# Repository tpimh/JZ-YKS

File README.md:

JZ-YKS
======

My first hardware mini-module

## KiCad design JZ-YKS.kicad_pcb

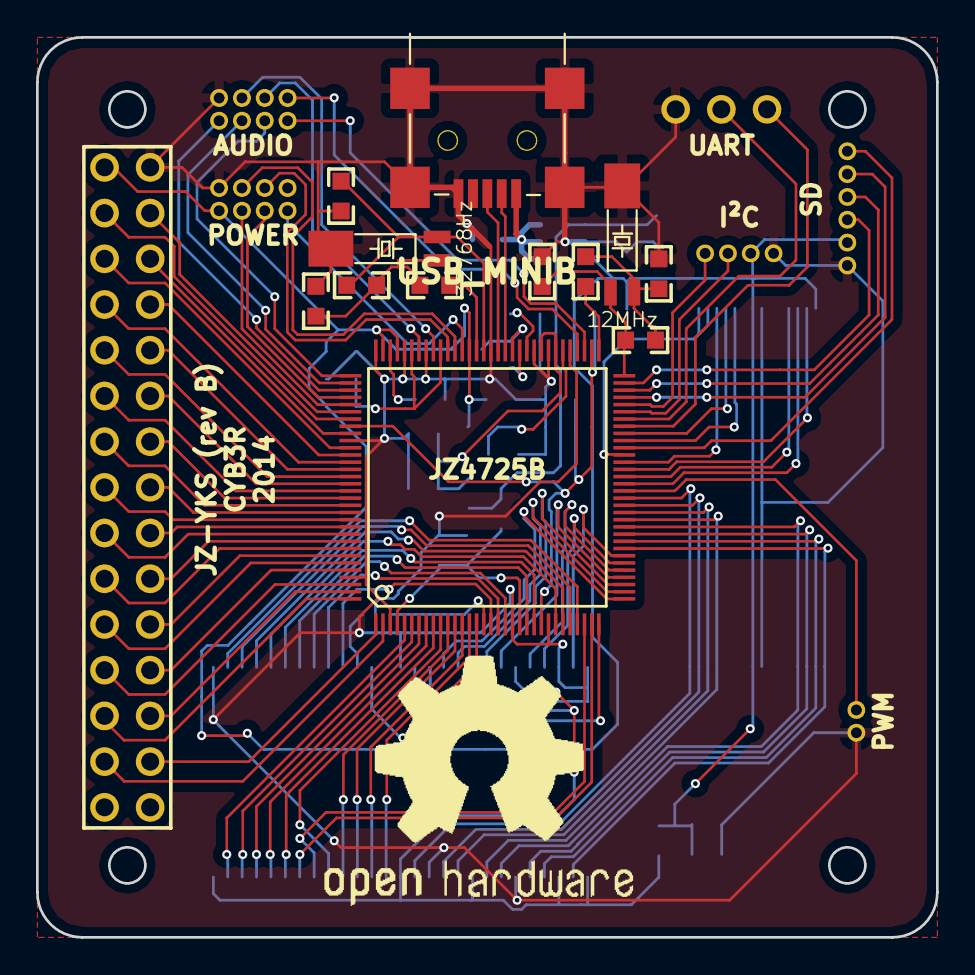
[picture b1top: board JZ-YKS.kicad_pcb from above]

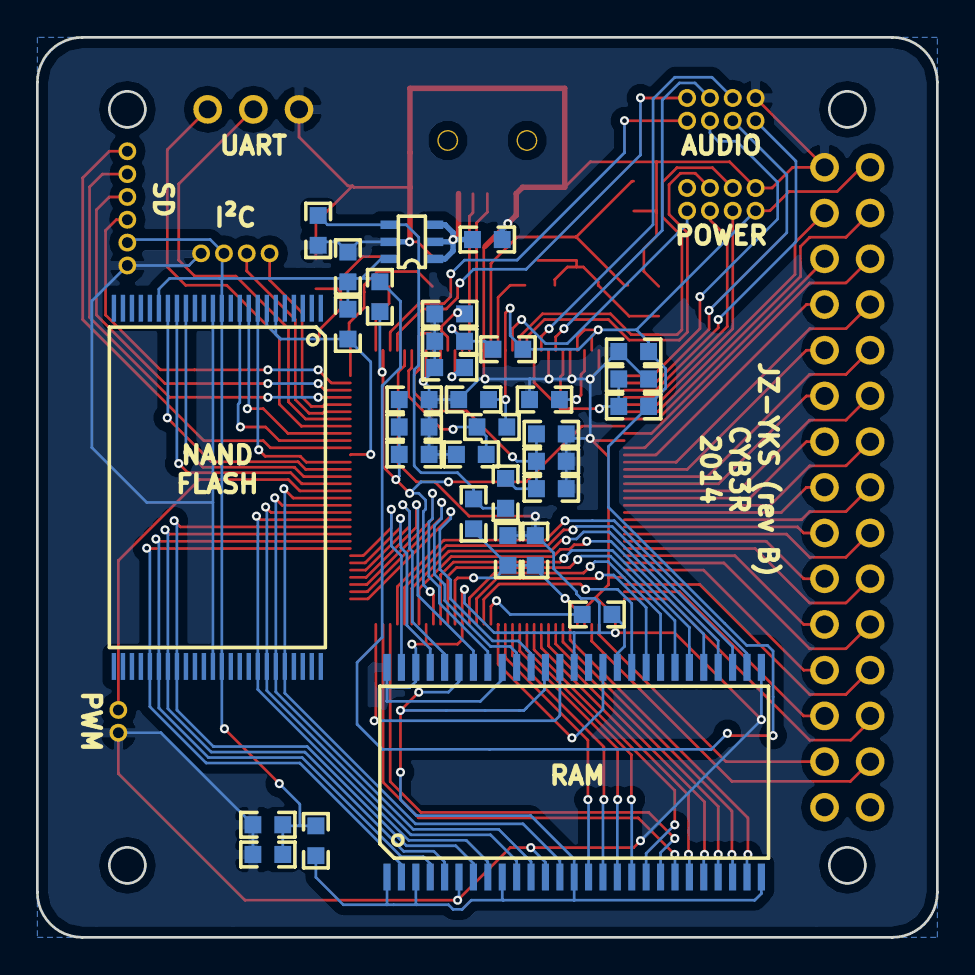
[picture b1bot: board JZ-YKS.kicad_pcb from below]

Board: 2 copper layers, 50.0 x 50.0 mm, 52 parts (33 on the bottom side), 116 nets.

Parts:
C1, C3, C4, C5, C9, C13, C27: 0.1uF; size-0603
C2, C6, C14, C15, C28: 10uF; size-0603
C7, C8, C10, C29, C30, C31: 1uF; size-0603
C11, C12: 0.01uF; size-0603
C16, C17, C18, C19: 22pF; size-0603
FB1, FB2, FB3, FB5, FB6, FB7, FB9: BKP1608HS121; size-0603
IC1: JZ4725; JZ-LQFP128
J1: USB_MINIB; CON_USB_MB
R1: 10k; size-0603
R2, R3, R6: 33; size-0603
R4: 10M; size-0603
R5: 1M; size-0603
R7: 100k; size-0603
U1: PINHEAD30; pinhead-double-2.54mm-30
U2, U9: PINHEAD8; pinhead-double-1.27mm-8
U3: VREG-DUAL; sot23-6
U4: HY27UG088G5M; tsop48
U5: P3V56S40ETP-G6; tsop54
U6: PINHEAD6; pinhead-1.27mm-6
U7: PINHEAD4; pinhead-1.27mm-4
U8: PINHEAD3; pinhead-2.54mm-3
U10: PINHEAD2; pinhead-1.27mm-2
X1: 32768Hz; crystal
X2: 12MHz; crystal

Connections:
+1.8V: C30.2, FB2.2, FB7.2, U3.4
+3.3V: C1.1, C11.1, C27.1, C28.1, C31.2, FB1.2, FB3.2, FB5.2, FB6.2, FB9.2, IC1.83, IC1.93, IC1.95, R7.1, U1.2, U2.2, U3.6, U4.12, U4.19, U4.37, U6.2, U7.2
/VDDCORE: C5.1, C6.1, FB2.1, IC1.4, IC1.21
/VDDIO: C2.1, C3.1, C4.1, FB1.1, IC1.24, IC1.66, IC1.104
/memory/MEM_VCC: FB9.1, U5.1, U5.3, U5.9, U5.14, U5.27, U5.43, U5.49
A0: IC1.8, U5.23
A1: IC1.7, U5.24
A2: IC1.6, U5.25
A3: IC1.5, U5.26
A4: IC1.29, U5.29
A5: IC1.28, U5.30
A6: IC1.27, U5.31
A7: IC1.26, U5.32
A8: IC1.23, U5.33
A9: IC1.22, U5.34
A10: IC1.9, U5.22
A11: IC1.19, U5.35
A12: IC1.18, U5.36
A13: IC1.30, U5.20
A14: IC1.31, U5.21
A15: IC1.50, U4.16
A16: IC1.49, U4.17
ADIN0: IC1.67, U9.8
ADIN1: IC1.68, U9.7
B1: IC1.105, U1.5
B2: IC1.1, U1.27
B3: IC1.128, U1.26
B4: IC1.127, U1.25
B5: IC1.126, U1.24
B6: IC1.124, U1.23
B7: IC1.123, U1.22
BOOT_0: IC1.101, U2.4
BOOT_1: IC1.100, U2.6
CAS: IC1.12, U5.17
CKE: IC1.17, U5.37
CKO: IC1.16, R6.2
CS1: IC1.56, U4.9
CS2: IC1.55, U4.10
D0: IC1.40, U4.29, U5.2
D1: IC1.41, U4.30, U5.4
D2: IC1.42, U4.31, U5.5
D3: IC1.43, U4.32, U5.7
D4: IC1.44, U4.41, U5.8
D5: IC1.45, U4.42, U5.10
D6: IC1.46, U4.43, U5.11
D7: IC1.47, U4.44, U5.13
D8: IC1.32, U5.42
D9: IC1.33, U5.44
D10: IC1.34, U5.45
D11: IC1.35, U5.47
D12: IC1.36, U5.48
D13: IC1.37, U5.50
D14: IC1.38, U5.51
D15: IC1.39, U5.53
DCS: IC1.10, U5.19
DE: IC1.110, U1.9
FRB: IC1.53, R7.2, U4.6, U4.7
FRE: IC1.52, U4.8
FWE: IC1.51, U4.18
G0: IC1.102, U1.3
G1: IC1.107, U1.6
G2: IC1.122, U1.21
G3: IC1.121, U1.20
G4: IC1.120, U1.19
G5: IC1.119, U1.18
G6: IC1.118, U1.17
G7: IC1.117, U1.16
GND: C1.2, C2.2, C3.2, C4.2, C5.2, C6.2, C7.2, C8.2, C9.2, C10.2, C11.2, C12.2, C13.2, C14.2, C15.2, C16.2, C17.2, C18.2, C19.2, C27.2, C28.2, C29.1, C30.1, C31.1, IC1.3, IC1.20, IC1.25, IC1.69, IC1.72, IC1.74, IC1.80, IC1.89, IC1.92, IC1.96, IC1.106, IC1.125, J1.5, J1.6, J1.7, J1.8, J1.9, R1.2, U1.1, U2.1, U3.5, U4.13, U4.36, U5.6, U5.12, U5.28, U5.41, U5.46, U5.52, U5.54, U6.1, U7.1, U8.3, U9.1, U10.2, X1.3, X2.3
HP_L: IC1.90, U9.5
HP_R: IC1.88, U9.3
HSYN: IC1.109, U1.8
IN_L: IC1.97, U9.6
IN_R: IC1.98, U9.4
MIC: IC1.99, U9.2
unnamed: IC1.65, R3.1
unnamed: IC1.82, R2.1
unnamed: C8.1, IC1.94
unnamed: IC1.76, R1.1
unnamed: C7.1, IC1.75
unnamed: IC1.79, J1.3
unnamed: IC1.78, J1.2
unnamed: C12.1, C13.1, C14.1, FB7.1, IC1.71, IC1.73
unnamed: C17.1, R2.2, R4.1, X1.1
unnamed: C18.1, IC1.81, R4.2, X1.2
unnamed: C16.1, IC1.64, R5.1, X2.1
unnamed: C19.1, R3.2, R5.2, X2.2
unnamed: C10.1, FB5.1, IC1.77
unnamed: C9.1, FB3.1, IC1.70
unnamed: C15.1, FB6.1, IC1.87, IC1.91
unnamed: R6.1, U5.38
PCLK: IC1.2, U1.28
PPRST: IC1.84, U2.8
PWM: IC1.48, U10.1
PWRON: IC1.86, U2.5
R1: IC1.103, U1.4
R2: IC1.116, U1.15
R3: IC1.115, U1.14
R4: IC1.114, U1.13
R5: IC1.113, U1.12
R6: IC1.112, U1.11
R7: IC1.111, U1.10
RAS: IC1.11, U5.18
RDWR: IC1.13, U5.16
RXD: IC1.57, U8.1
SCK: IC1.59, U7.3
SDA: IC1.60, U7.4
SD_CD: IC1.54, U6.6
SD_CLK: IC1.62, U6.4
SD_CMD: IC1.63, U6.3
SD_DO: IC1.61, U6.5
TXD: IC1.58, U8.2
VCC: C29.2, J1.1, U3.1, U3.2, U3.3
VSYN: IC1.108, U1.7
WE0: IC1.14, U5.15
WE1: IC1.15, U5.39
WKUP: IC1.85, U2.3

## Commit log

2013-08-29 here is what I have now
2013-08-29 libraries in lib and modules in mod path
2013-08-29 added oscillators from qi-hardware
2013-08-29 redrawn a little from Volans schematics
2013-08-29 components enumeration for netlist
2013-08-29 netlist
2013-08-29 added modules for hardware design
2013-08-30 first attempt to place everything on one board
2013-08-30 get rid of backup files and empty documentation files
2013-08-30 added some vias
2013-08-31 added lcd connector
2013-08-31 no more testpoints
2013-08-31 header for I2C and UART
2013-08-31 lcd and i2c/uart connectors
2013-08-31 all pinhead connectors in one file
2013-08-31 new netlist generated
2013-08-31 quickfix
2013-08-31 audio connector
2013-09-06 usb added
2013-09-06 memory added
2013-09-07 memory connected
2013-09-07 sd card header
2013-09-10 old board layout sucks
2013-09-10 just two 30pin connectors
2013-09-10 module cleanup
2013-09-10 pcb version 2
2013-09-10 another layout with funky 45 degree rotation
2013-09-14 fixed wrong voltage and some improvements
2013-09-17 pinheads are now connected
2013-09-24 added dual-channel LDO
2013-11-05 changed the vreg
2013-11-05 final version of the board (goes to production)
2014-01-12 new TSOP modules
2014-01-14 that fucking TSOP library is all wrong
2014-01-14 rebirth of the pcb
2014-01-14 now fixed that fucking output numeration for TSOP
2014-01-14 RAM and NAND successfully routed
2014-01-15 far from ideal, but still ready for production
2014-02-10 final fixes for rev.A
2014-02-10 deleted unused footprints
2014-03-25 rev.A that was actualy manufactured
2014-05-18 rev.B with few vital fixes
